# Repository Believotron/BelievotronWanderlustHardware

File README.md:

# Believotron Wanderlust Hardware
The source and output files for the Believotron Wanderlust synthesizer controller.

For more information:
http://believotron.com
http://community.believotron.community

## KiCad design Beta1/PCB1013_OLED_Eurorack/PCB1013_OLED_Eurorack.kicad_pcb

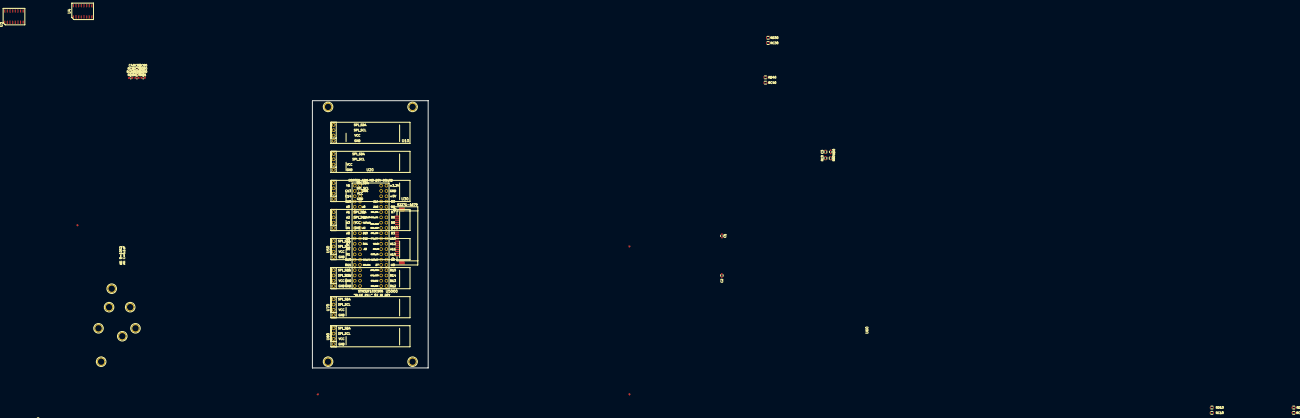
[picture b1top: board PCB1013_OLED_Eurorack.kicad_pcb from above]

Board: 2 copper layers, 55.6 x 128.5 mm, 38 parts (0 on the bottom side), 25 nets, no tracks yet.

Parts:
C1, C2, C3: 0.1u; C_0603
C4: 0.1u; C_0603_1608Metric
J2: FPC_20POS; FFC_1MM_20POS_MOLEX_52271-2079
RC0, RC10, RC20, RC30, RC40: 10K; R_0603
RC1, RC50, RC60, RC70, RC80: 10K; R_0603_1608Metric
RD0, RD10, RD20, RD30, RD40: 10K; R_0603
RD1, RD50, RD60, RD70, RD80: 10K; R_0603_1608Metric
RR0: 10K; R_0603
RR1: 10K; R_0603_1608Metric
U3, U4: I2C_1x4MUX_TCA9546A; SOIC-16_1.27x5.4
U10, U20, U30, U40, U50, U60, U70, U80: OLED_128x32_I2C; OLED_128x32
U5000: STM32F103C8T6_BLUE_PILL; BLUEPILL_CORTEXM3_STM32F103C8T6_THIN

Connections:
+3V3: C1.1, C2.1, C3.1, C4.1, J2.19, J2.20, RC0.1, RC1.1, RC10.1, RC20.1, RC30.1, RC40.1, RC50.1, RC60.1, RC70.1, RC80.1, RD0.1, RD1.1, RD10.1, RD20.1, RD30.1, RD40.1, RD50.1, RD60.1, RD70.1, RD80.1, RR0.1, RR1.1, U3.16, U4.16, U10.2, U20.2, U30.2, U40.2, U50.2, U60.2, U70.2, U80.2, U5000.3.3V
/!OLED_RESET: RR0.2, RR1.2, U3.3, U4.3, U5000.A7
/I2C_SCL0: RC10.2, U3.5, U10.3
/I2C_SCL1: RC20.2, U3.7, U20.3
/I2C_SCL2: RC30.2, U3.10, U30.3
/I2C_SCL3: RC40.2, U3.12, U40.3
/I2C_SCL4: RC50.2, U4.5, U50.3
/I2C_SCL5: RC60.2, U4.7, U60.3
/I2C_SCL6: RC70.2, U4.10, U70.3
/I2C_SCL7: RC80.2, U4.12, U80.3
/I2C_SCL_EXT: RC0.2, RC1.2, U3.14, U4.14, U5000.B10
/I2C_SDA0: RD10.2, U3.4, U10.4
/I2C_SDA1: RD20.2, U3.6, U20.4
/I2C_SDA2: RD30.2, U3.9, U30.4
/I2C_SDA3: RD40.2, U3.11, U40.4
/I2C_SDA4: RD50.2, U4.4, U50.4
/I2C_SDA5: RD60.2, U4.6, U60.4
/I2C_SDA6: RD70.2, U4.9, U70.4
/I2C_SDA7: RD80.2, U4.11, U80.4
/I2C_SDA_AXO: J2.4, U5000.B7
/I2C_SDA_EXT: RD0.2, RD1.2, U3.15, U4.15, U5000.B11
/RESET_AXO: J2.17, U5000.R
/RX_AXO: J2.8, U5000.A9
/TX_AXO: J2.9, U5000.A10
GND: C1.2, C2.2, C3.2, C4.2, J2.1, J2.2, U3.1, U3.2, U3.8, U3.13, U4.2, U4.8, U4.13, U10.1, U20.1, U30.1, U40.1, U50.1, U60.1, U70.1, U80.1, U5000.GND

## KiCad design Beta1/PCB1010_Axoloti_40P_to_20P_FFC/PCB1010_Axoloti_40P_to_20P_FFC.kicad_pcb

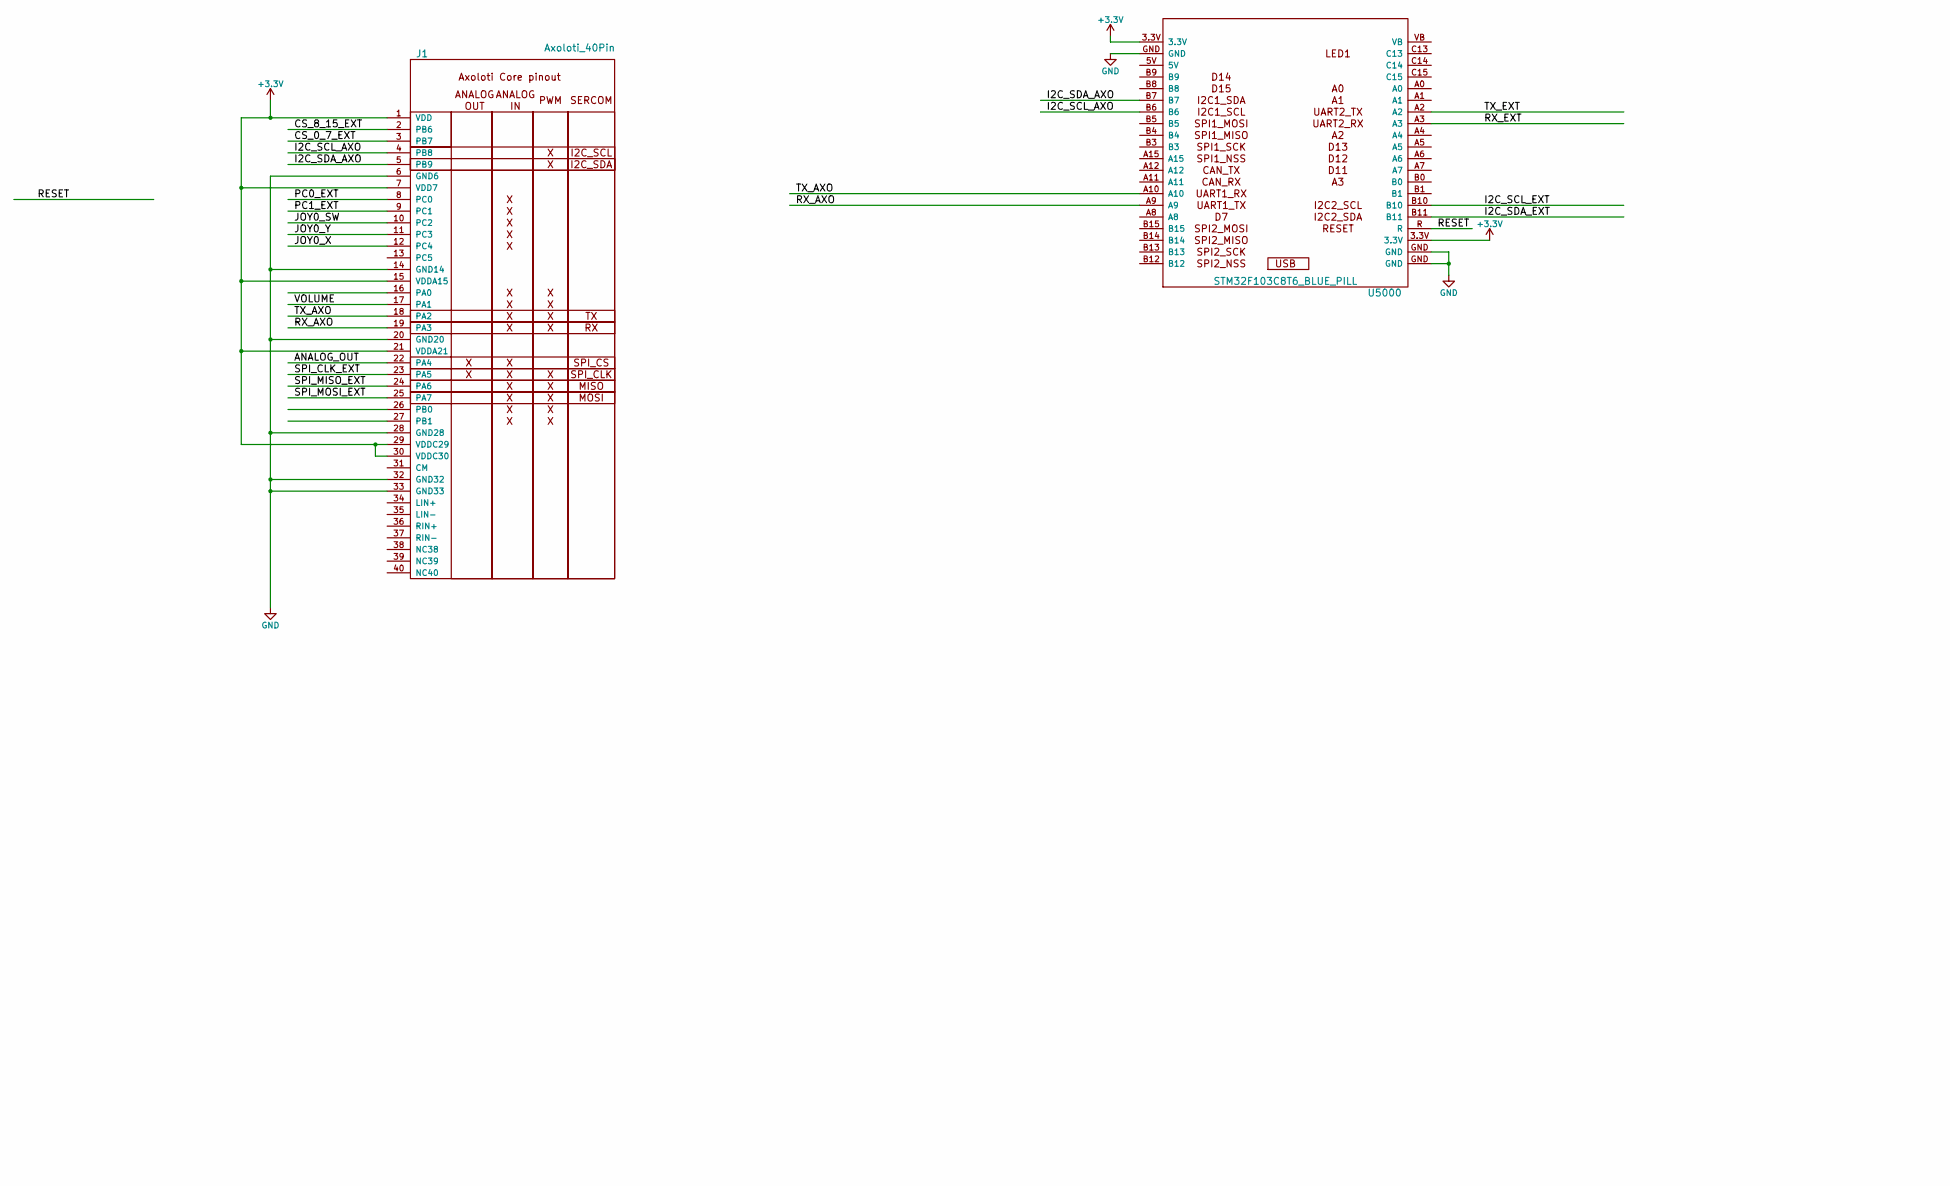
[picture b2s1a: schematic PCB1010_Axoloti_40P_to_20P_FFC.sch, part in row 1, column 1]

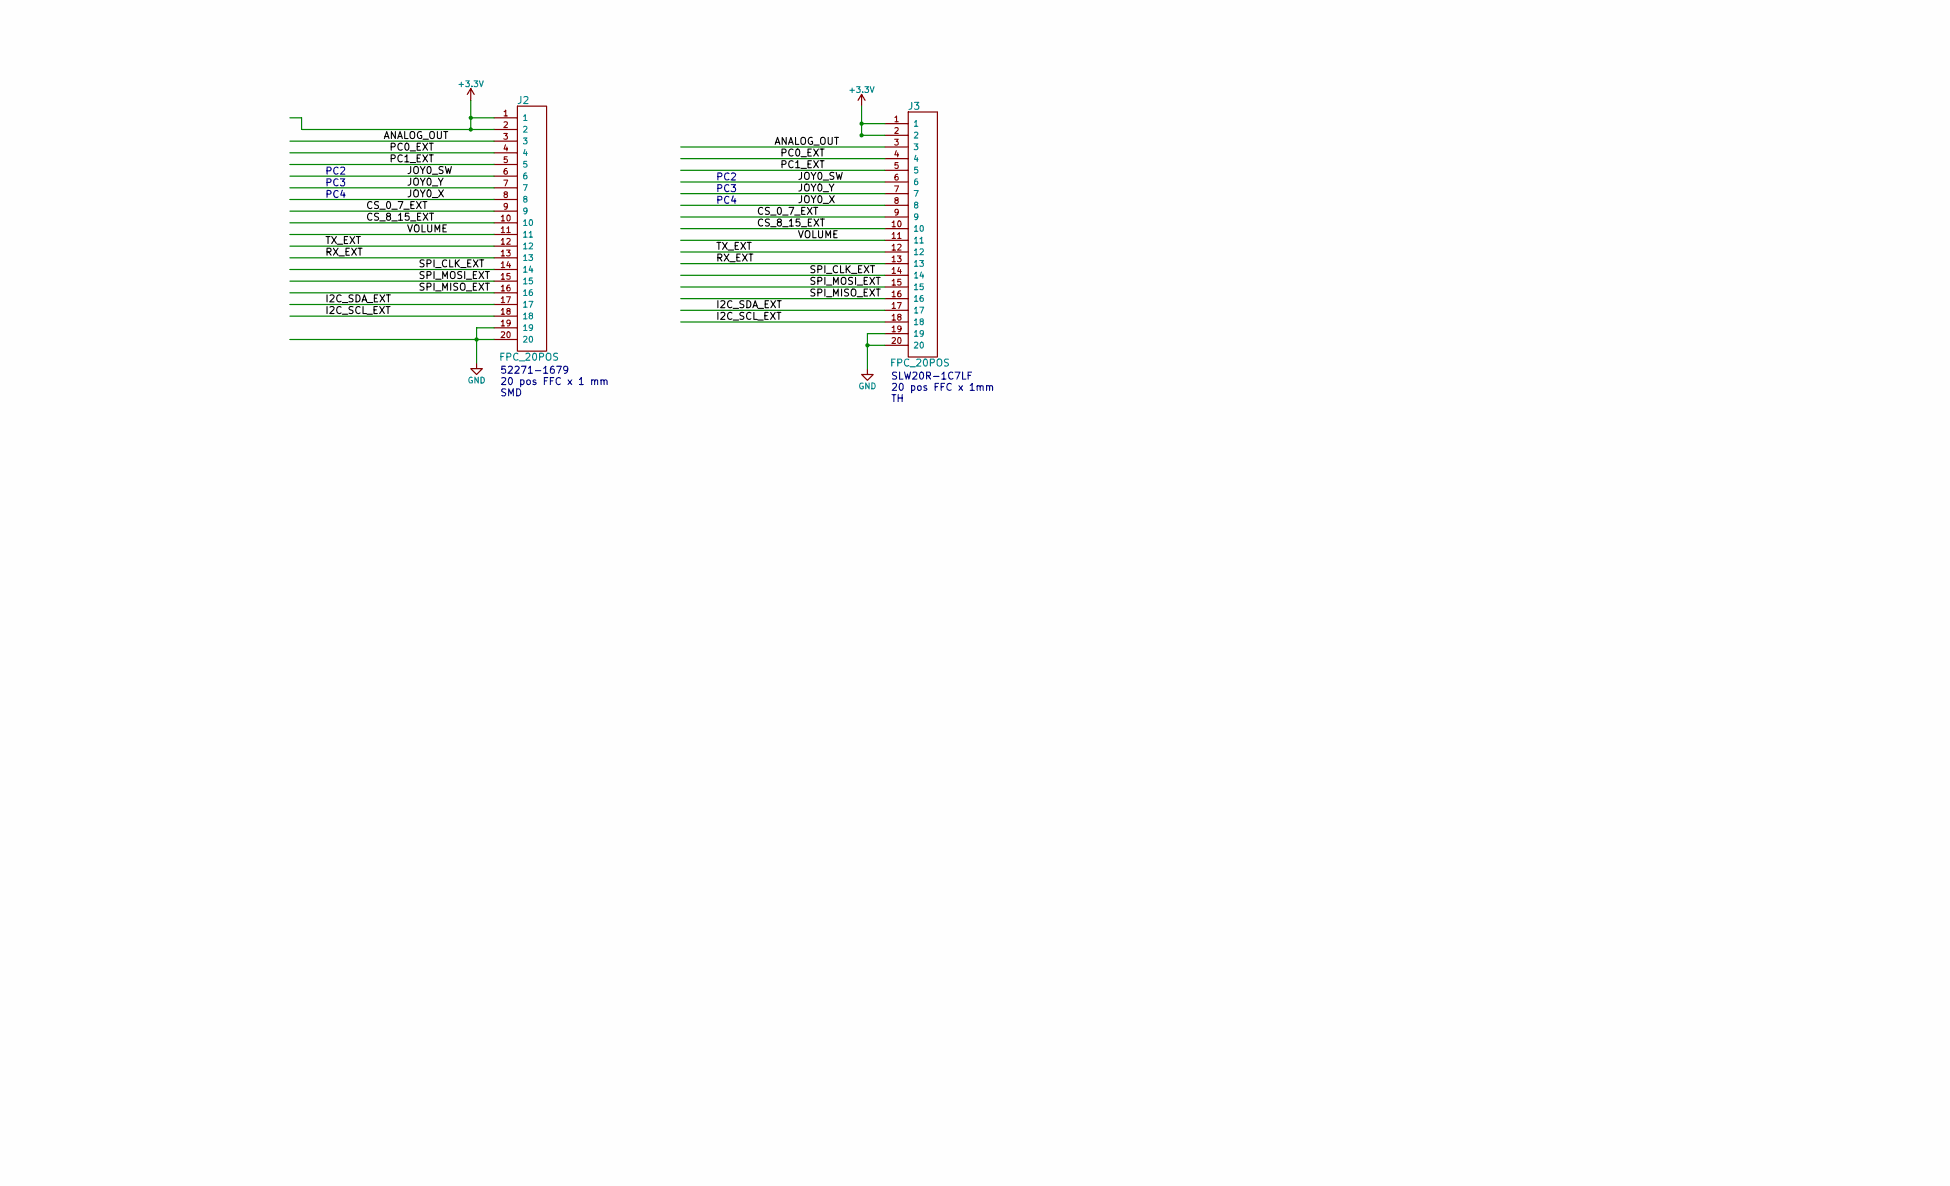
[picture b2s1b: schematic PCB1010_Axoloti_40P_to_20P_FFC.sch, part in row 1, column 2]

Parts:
J1: Axoloti_40Pin; Axoloti-40x2_slim
J2: FPC_20POS; FFC_1MM_20POS_MOLEX_52271-2079
J3: FPC_20POS; FFC_20x1mm_SLW20R-1C7LF
U5000: STM32F103C8T6_BLUE_PILL; BLUEPILL_CORTEXM3_STM32F103C8T6_THIN

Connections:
+3V3: J1.1 (VDD), J1.7 (VDD7), J1.15 (VDDA15), J1.21 (VDDA21), J1.29 (VDDC29), J1.30 (VDDC30), J2.1, J2.2, J3.1, J3.2, U5000.3.3V
/ANALOG_OUT: J1.22 (PA4), J2.3, J3.3
/CS_0_7_EXT: J1.3 (PB7), J2.9, J3.9
/CS_8_15_EXT: J1.2 (PB6), J2.10, J3.10
/I2C_SCL_AXO: J1.4 (PB8), U5000.B6
/I2C_SCL_EXT: J2.18, J3.18, U5000.B10
/I2C_SDA_AXO: J1.5 (PB9), U5000.B7
/I2C_SDA_EXT: J2.17, J3.17, U5000.B11
/JOY0_SW: J1.10 (PC2), J2.6, J3.6
/JOY0_X: J1.12 (PC4), J2.8, J3.8
/JOY0_Y: J1.11 (PC3), J2.7, J3.7
/PC0_EXT: J1.8 (PC0), J2.4, J3.4
/PC1_EXT: J1.9 (PC1), J2.5, J3.5
/RESET: U5000.R
/RX_AXO: J1.19 (PA3), U5000.A9
/RX_EXT: J2.13, J3.13, U5000.A3
/SPI_CLK_EXT: J1.23 (PA5), J2.14, J3.14
/SPI_MISO_EXT: J1.24 (PA6), J2.16, J3.16
/SPI_MOSI_EXT: J1.25 (PA7), J2.15, J3.15
/TX_AXO: J1.18 (PA2), U5000.A10
/TX_EXT: J2.12, J3.12, U5000.A2
/VOLUME: J1.17 (PA1), J2.11, J3.11
GND: J1.6 (GND6), J1.14 (GND14), J1.20 (GND20), J1.28 (GND28), J1.32 (GND32), J1.33 (GND33), J2.19, J2.20, J3.19, J3.20, U5000.GND

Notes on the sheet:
2017-06-07
Believotron KnobCore 8CH Knob + Vol + 4CH Joy + 3CH OLED
Open source via MIT License github.com/Believotron/BelievotronWanderlustHardware
Date
PC2
PC3
PC4
SLW20R-1C7LF 20 pos FFC x 1mm TH
52271-1679 20 pos FFC x 1 mm SMD

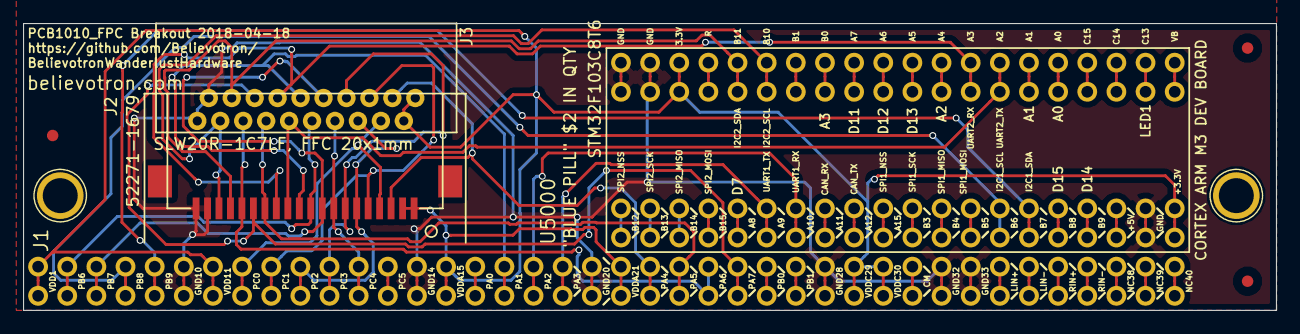
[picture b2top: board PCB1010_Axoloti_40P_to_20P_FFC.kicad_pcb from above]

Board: 2 copper layers, 109.2 x 25.0 mm, 4 parts (0 on the bottom side), 22 nets.

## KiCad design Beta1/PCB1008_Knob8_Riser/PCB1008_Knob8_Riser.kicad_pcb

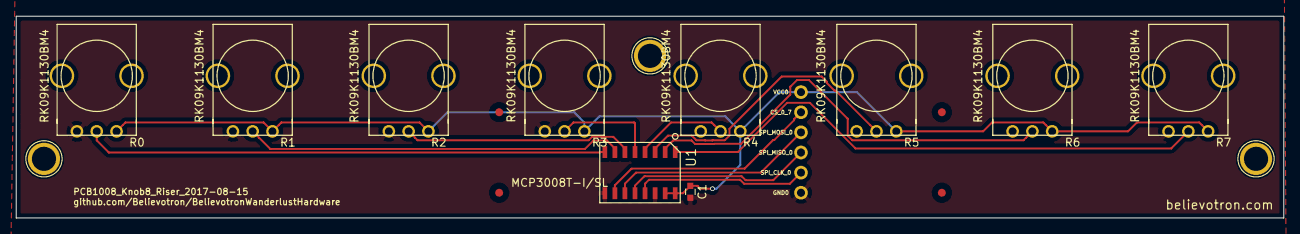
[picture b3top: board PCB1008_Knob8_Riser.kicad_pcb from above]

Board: 2 copper layers, 160.0 x 25.5 mm, 16 parts (0 on the bottom side), 14 nets.

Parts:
C1: 0.1u; C_0603
CS_0_7: CONN_01X01; single_0.1
GND0: CONN_01X01; single_0.1
R0, R1, R2, R3, R4, R5, R6, R7: POT; POT_ALPS_RK09K1130BM4
SPI_CLK_0: CONN_01X01; single_0.1
SPI_MISO_0: CONN_01X01; single_0.1
SPI_MOSI_0: CONN_01X01; single_0.1
U1: MCP3008T-I/SL; SOIC-16
VCC0: CONN_01X01; single_0.1

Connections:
+3V3: C1.1, R0.1, R1.1, R2.1, R3.1, R4.1, R5.1, R6.1, R7.1, U1.15, U1.16, VCC0.1
/CS_0_7: CS_0_7.1, U1.10
/P0: R0.2, U1.8
/P1: R1.2, U1.7
/P2: R2.2, U1.6
/P3: R3.2, U1.5
/P4: R4.2, U1.4
/P5: R5.2, U1.3
/P6: R6.2, U1.2
/P7: R7.2, U1.1
/SPI_CLK: SPI_CLK_0.1, U1.13
/SPI_MISO: SPI_MISO_0.1, U1.12
/SPI_MOSI: SPI_MOSI_0.1, U1.11
GND: C1.2, GND0.1, R0.3, R1.3, R2.3, R3.3, R4.3, R5.3, R6.3, R7.3, U1.9, U1.14

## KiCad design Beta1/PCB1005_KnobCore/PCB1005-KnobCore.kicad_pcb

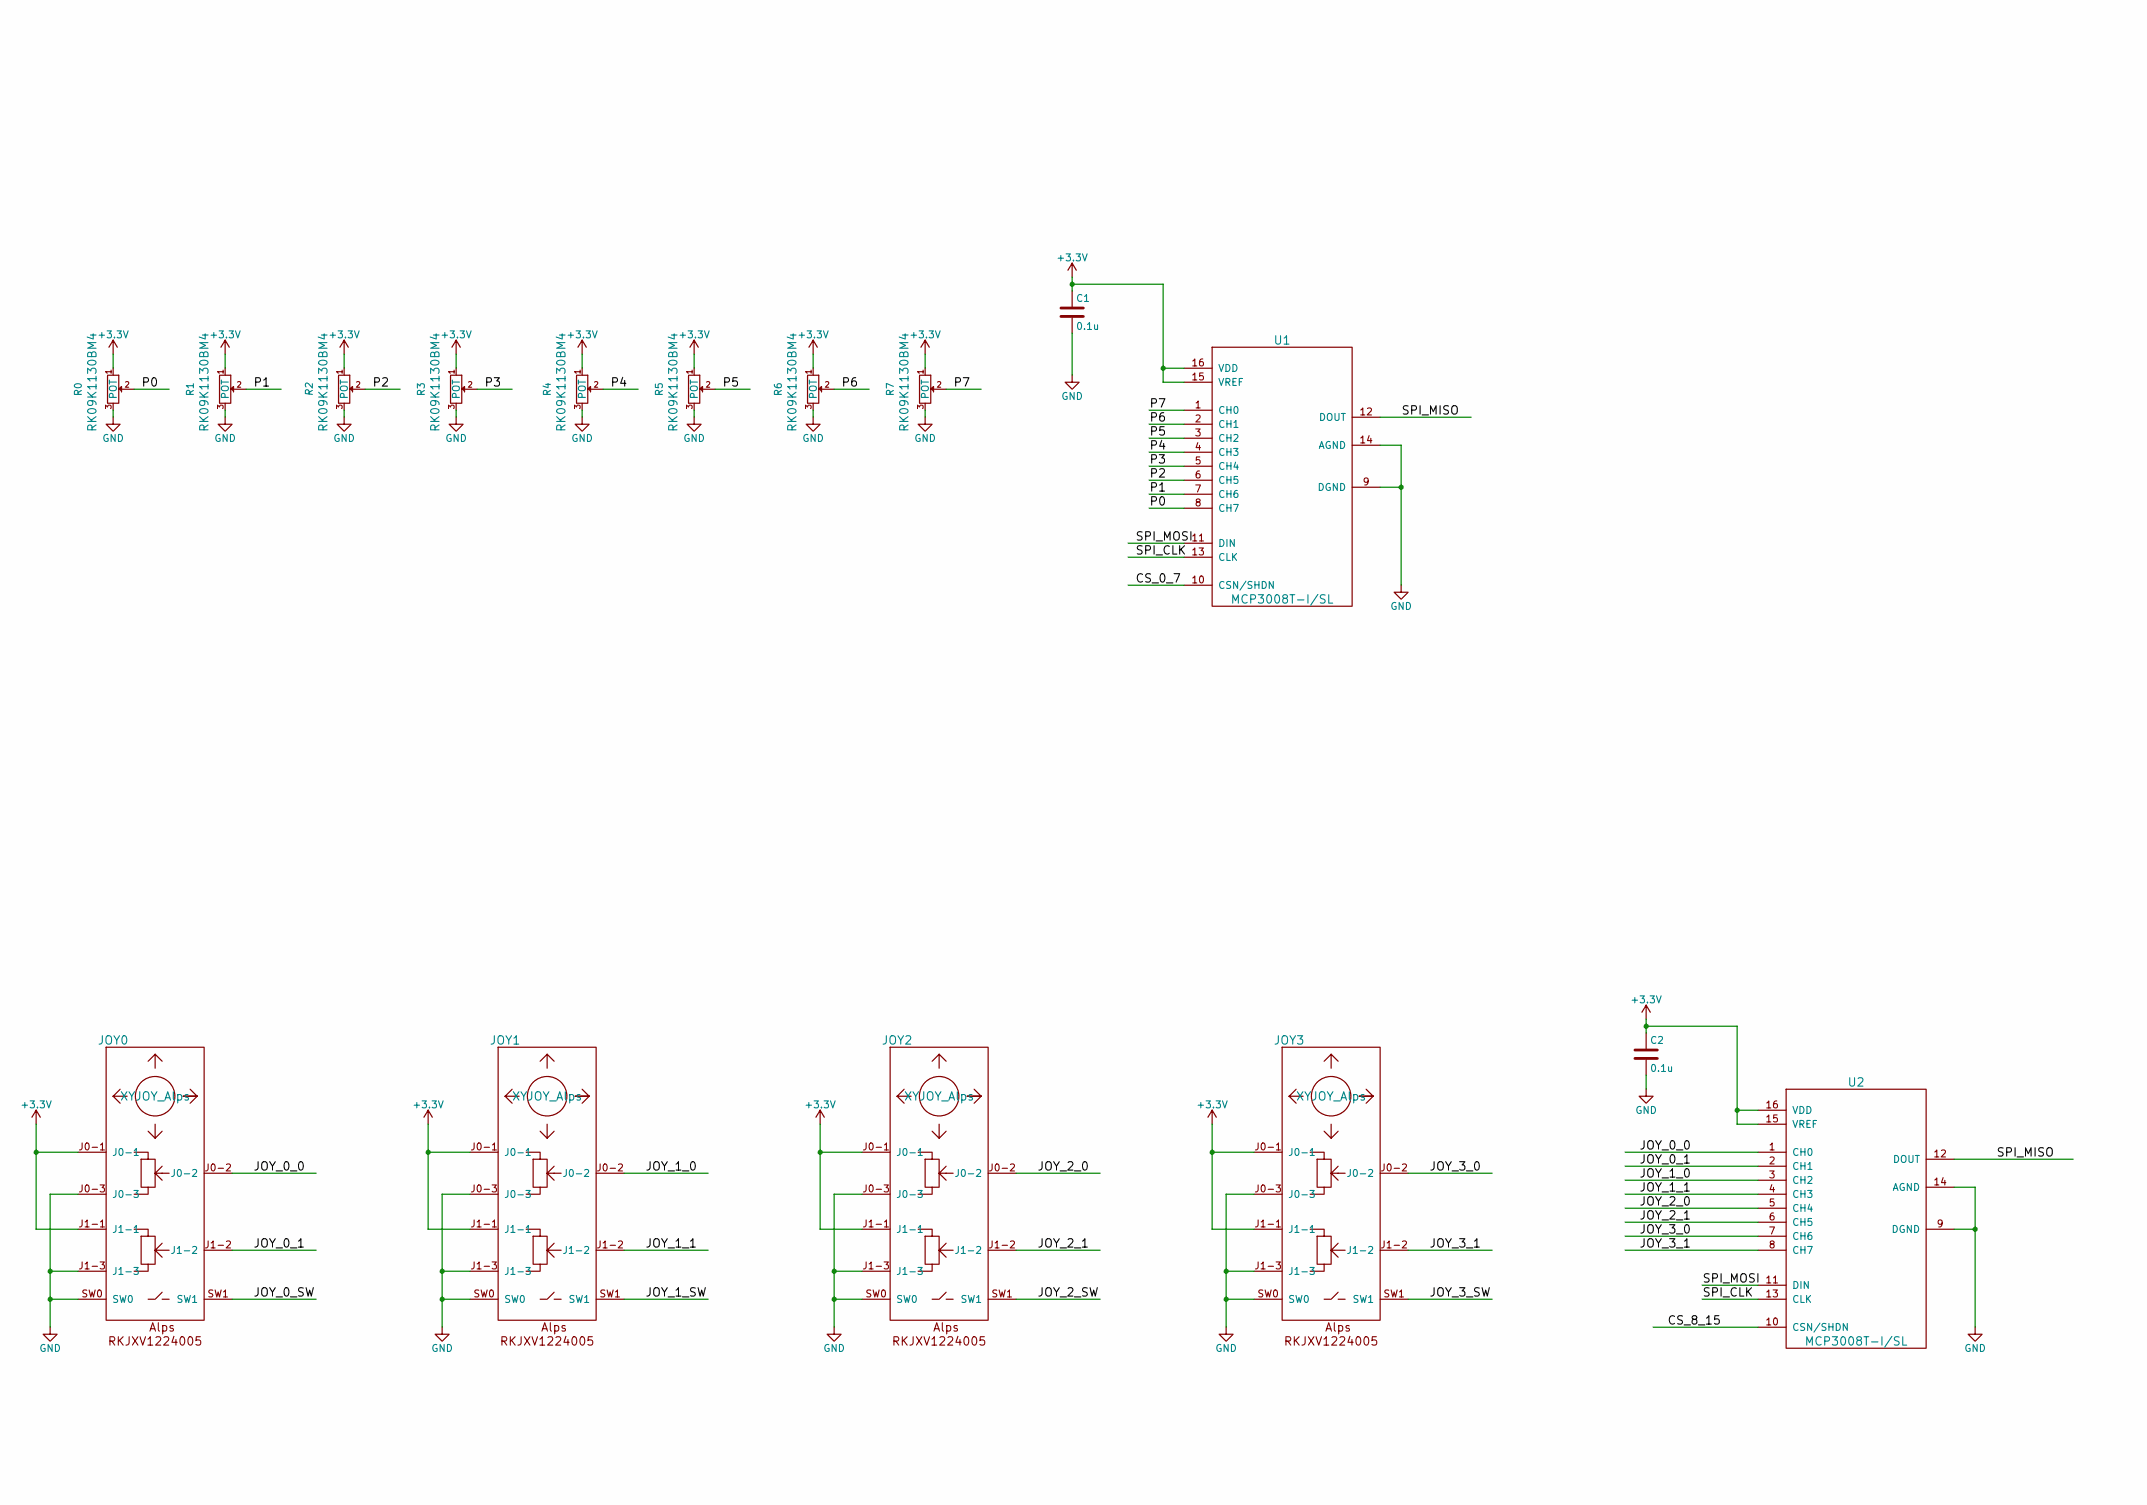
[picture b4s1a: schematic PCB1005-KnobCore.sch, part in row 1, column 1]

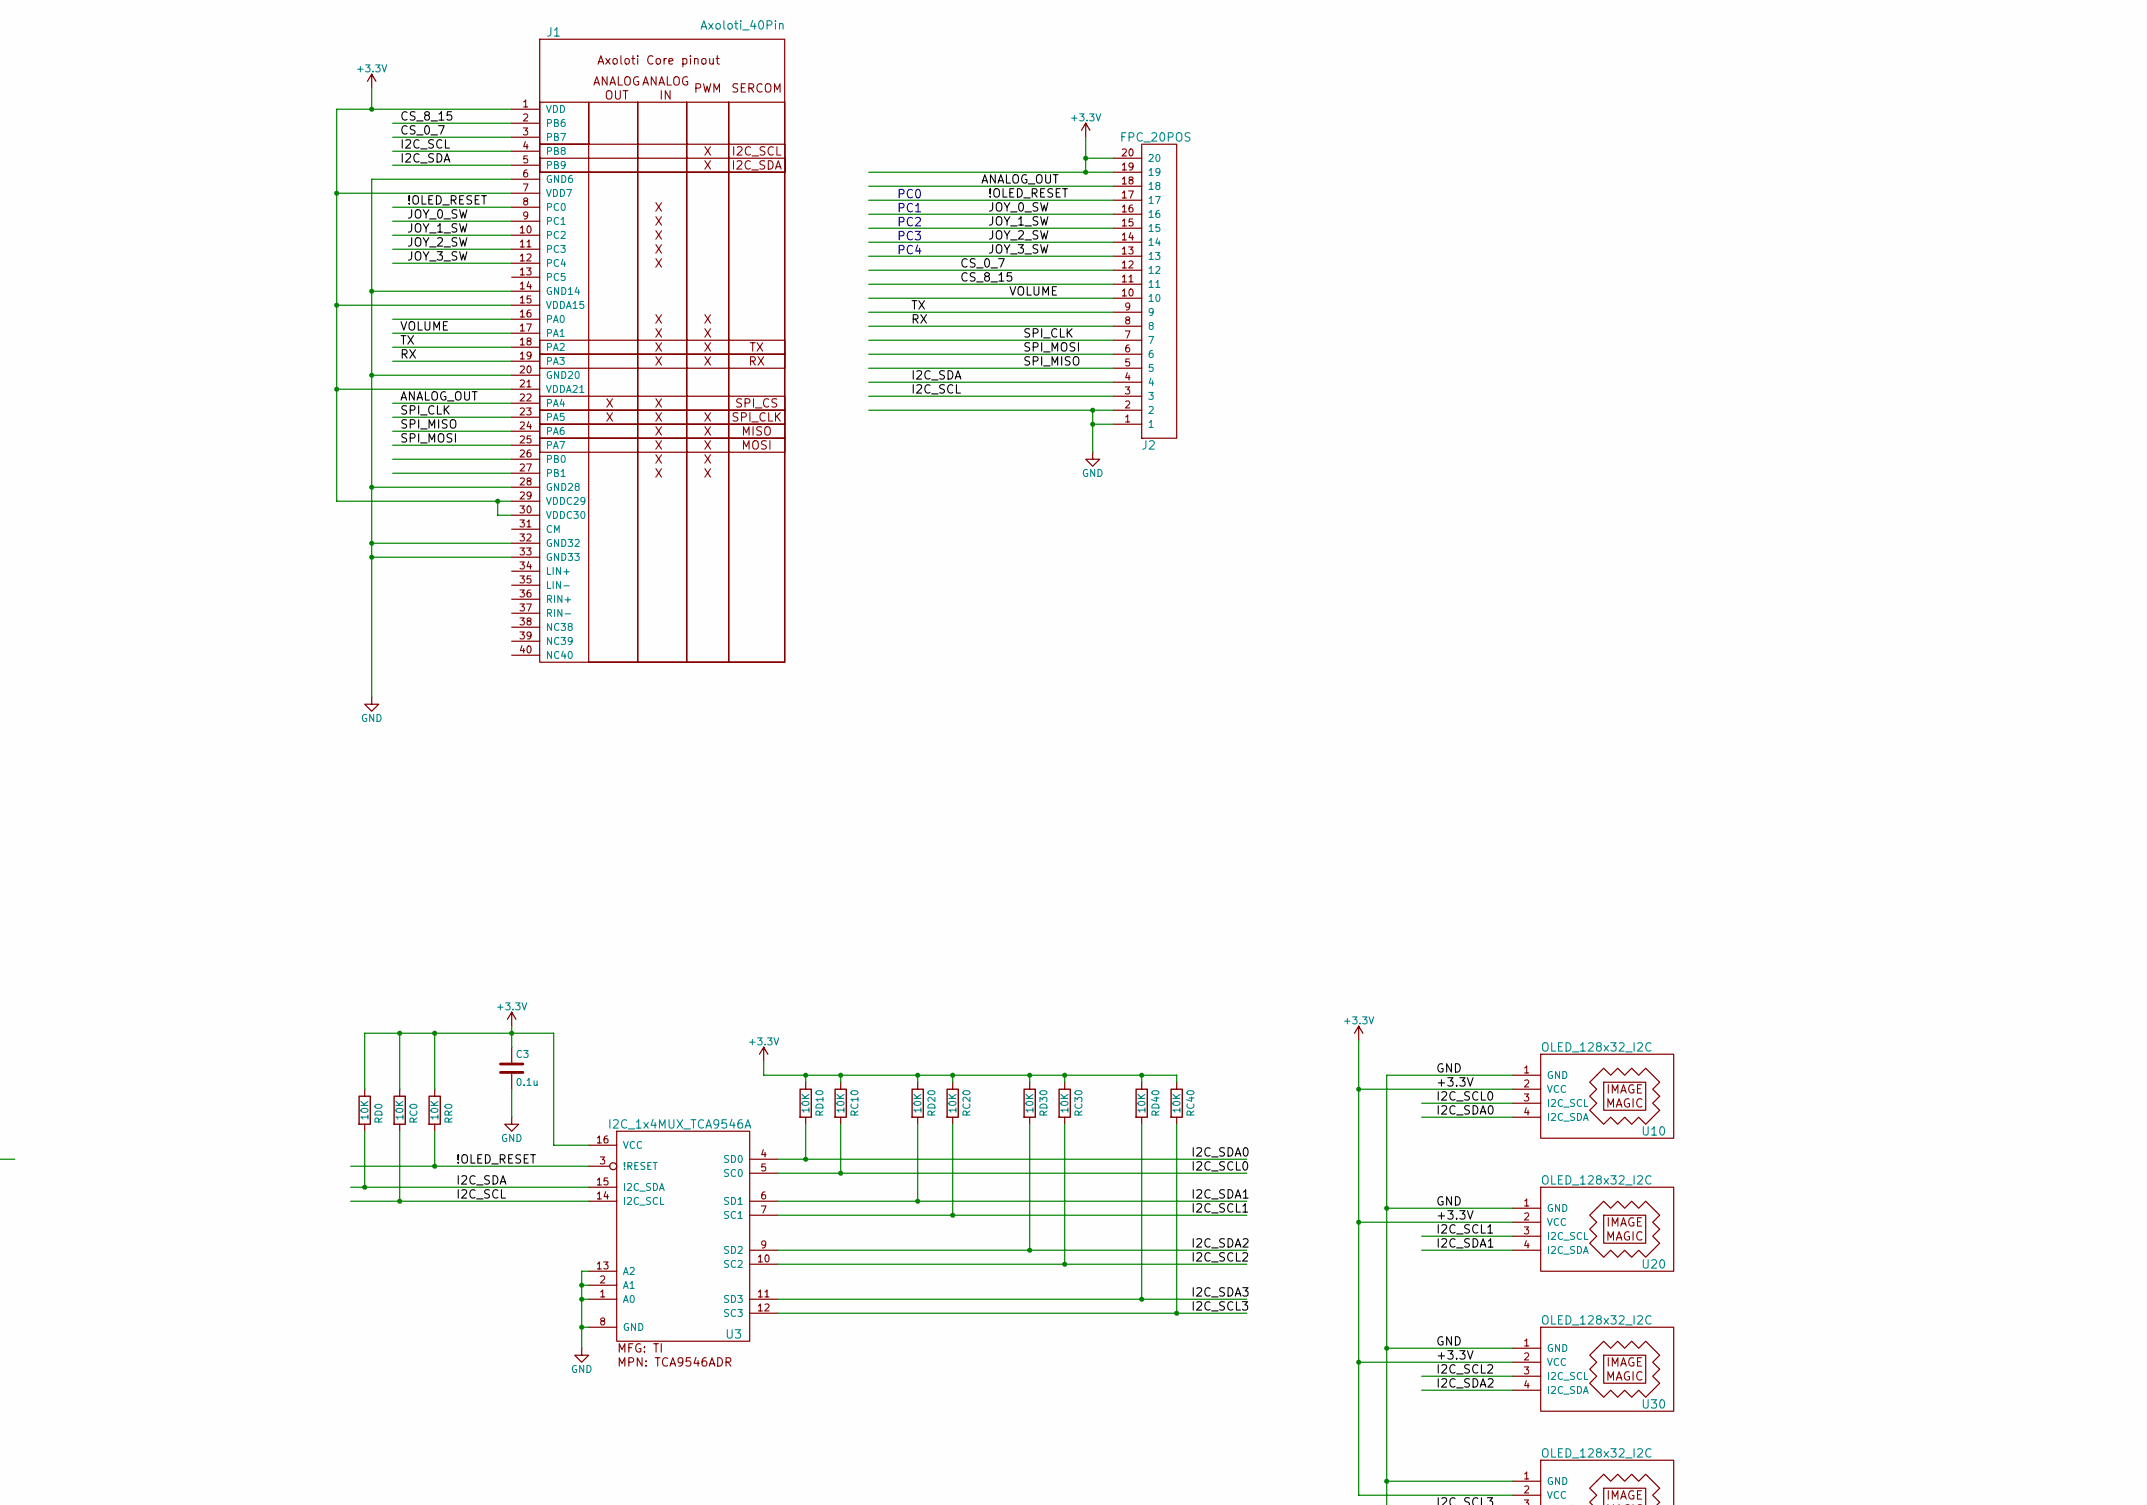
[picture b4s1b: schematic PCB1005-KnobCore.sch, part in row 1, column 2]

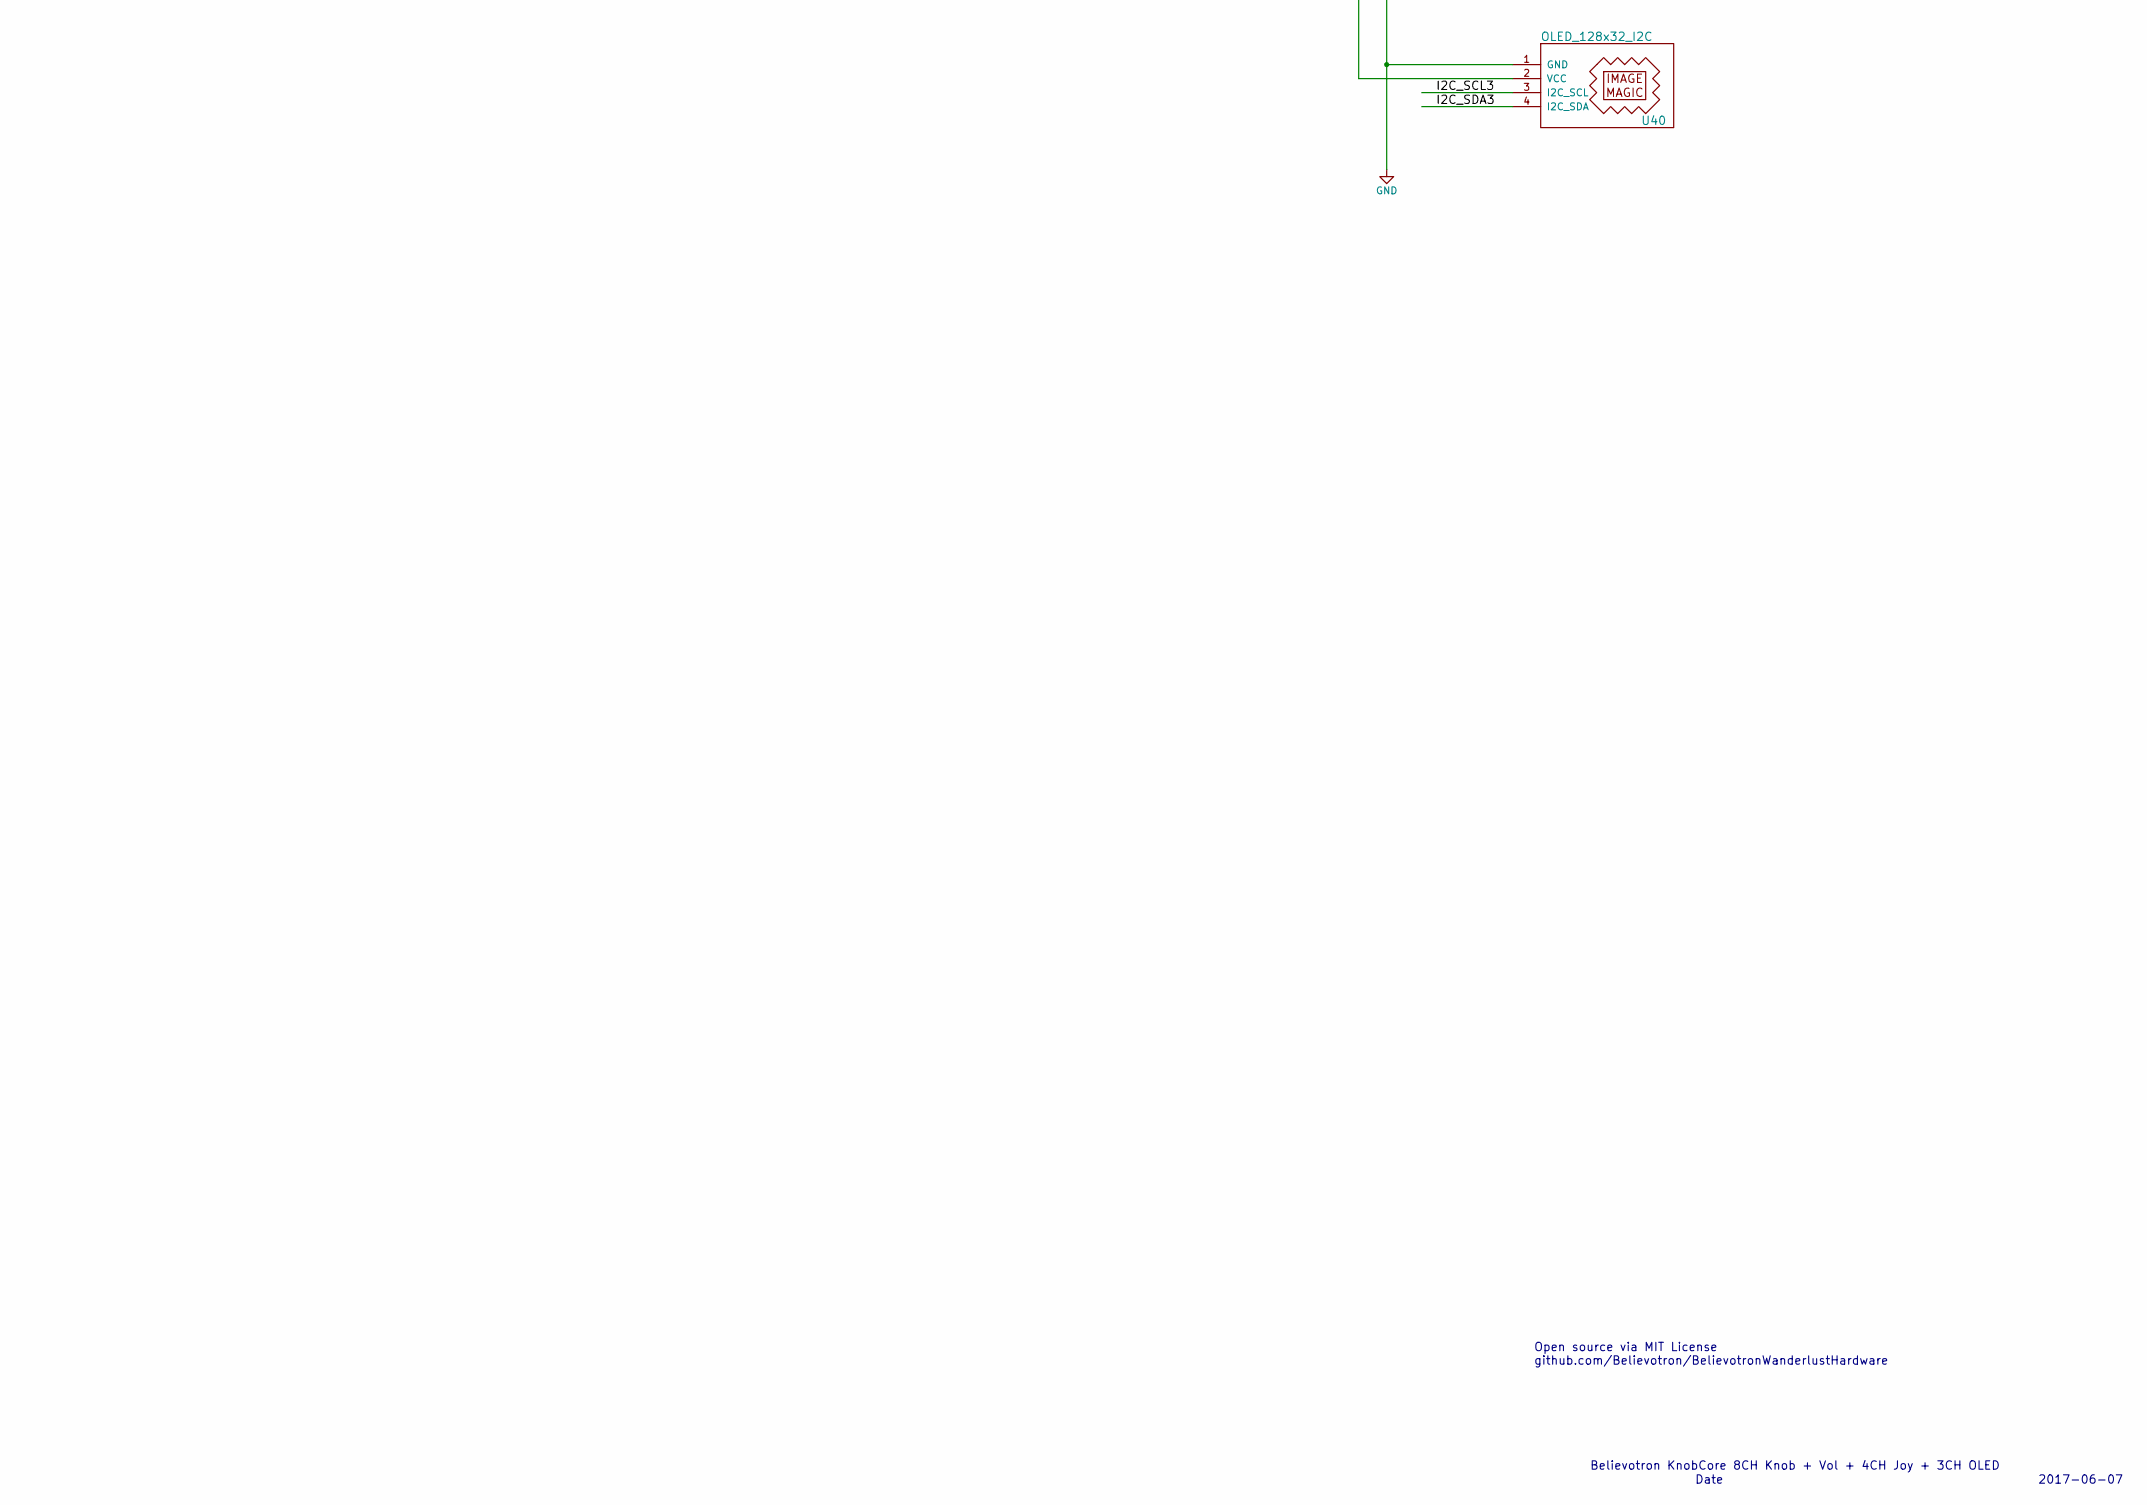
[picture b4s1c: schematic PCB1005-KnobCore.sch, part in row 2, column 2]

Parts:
C1, C2, C3: 0.1u; C_0603; MPN CC0603KRX7R9BB104
J1: Axoloti_40Pin; Axoloti-40x1_slim
J2: FPC_20POS; FFC_1MM_20POS_MOLEX_52271-2079
JOY0, JOY1, JOY2, JOY3: XYJOY_Alps; JOY_ALPS_RKJXV1224005
R0, R1, R2, R3, R4, R5, R6, R7: POT; POT_ALPS_RK09K1130BM4; MPN RK09K1130BM4
RC0, RC10, RC20, RC30, RC40: 10K; R_0603; MPN CRCW060310K0JNEA
RD0, RD10, RD20, RD30, RD40: 10K; R_0603; MPN CRCW060310K0JNEA
RR0: 10K; R_0603; MPN CRCW060310K0JNEA
U1, U2: MCP3008T-I/SL; SOIC-16; MPN MCP3008T-I/SL
U3: I2C_1x4MUX_TCA9546A; SOIC-16_1.27x5.4
U10, U20, U30, U40: OLED_128x32_I2C; OLED_128x32

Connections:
+3V3: C1.1, C2.1, C3.1, J1.1 (VDD), J1.7 (VDD7), J1.15 (VDDA15), J1.21 (VDDA21), J1.29 (VDDC29), J1.30 (VDDC30), J2.19, J2.20, JOY0.J0-1, JOY0.J1-1, JOY1.J0-1, JOY1.J1-1, JOY2.J0-1, JOY2.J1-1, JOY3.J0-1, JOY3.J1-1, R0.1, R1.1, R2.1, R3.1, R4.1, R5.1, R6.1, R7.1, RC0.1, RC10.1, RC20.1, RC30.1, RC40.1, RD0.1, RD10.1, RD20.1, RD30.1, RD40.1, RR0.1, U1.15 (VREF), U1.16 (VDD), U2.15 (VREF), U2.16 (VDD), U3.16 (VCC), U10.2 (VCC), U20.2 (VCC), U30.2 (VCC), U40.2 (VCC)
/!OLED_RESET: J1.8 (PC0), J2.17, RR0.2, U3.3 (!RESET)
/ANALOG_OUT: J1.22 (PA4), J2.18
/CS_0_7: J1.3 (PB7), J2.12, U1.10 (CSN/SHDN)
/CS_8_15: J1.2 (PB6), J2.11, U2.10 (CSN/SHDN)
/I2C_SCL: J1.4 (PB8), J2.3, RC0.2, U3.14 (I2C_SCL)
/I2C_SCL0: RC10.2, U3.5 (SC0), U10.3 (I2C_SCL)
/I2C_SCL1: RC20.2, U3.7 (SC1), U20.3 (I2C_SCL)
/I2C_SCL2: RC30.2, U3.10 (SC2), U30.3 (I2C_SCL)
/I2C_SCL3: RC40.2, U3.12 (SC3), U40.3 (I2C_SCL)
/I2C_SDA: J1.5 (PB9), J2.4, RD0.2, U3.15 (I2C_SDA)
/I2C_SDA0: RD10.2, U3.4 (SD0), U10.4 (I2C_SDA)
/I2C_SDA1: RD20.2, U3.6 (SD1), U20.4 (I2C_SDA)
/I2C_SDA2: RD30.2, U3.9 (SD2), U30.4 (I2C_SDA)
/I2C_SDA3: RD40.2, U3.11 (SD3), U40.4 (I2C_SDA)
/JOY_0_0: JOY0.J0-2, U2.1 (CH0)
/JOY_0_1: JOY0.J1-2, U2.2 (CH1)
/JOY_0_SW: J1.9 (PC1), J2.16, JOY0.SW1
/JOY_1_0: JOY1.J0-2, U2.3 (CH2)
/JOY_1_1: JOY1.J1-2, U2.4 (CH3)
/JOY_1_SW: J1.10 (PC2), J2.15, JOY1.SW1
/JOY_2_0: JOY2.J0-2, U2.5 (CH4)
/JOY_2_1: JOY2.J1-2, U2.6 (CH5)
/JOY_2_SW: J1.11 (PC3), J2.14, JOY2.SW1
/JOY_3_0: JOY3.J0-2, U2.7 (CH6)
/JOY_3_1: JOY3.J1-2, U2.8 (CH7)
/JOY_3_SW: J1.12 (PC4), J2.13, JOY3.SW1
/P0: R0.2, U1.8 (CH7)
/P1: R1.2, U1.7 (CH6)
/P2: R2.2, U1.6 (CH5)
/P3: R3.2, U1.5 (CH4)
/P4: R4.2, U1.4 (CH3)
/P5: R5.2, U1.3 (CH2)
/P6: R6.2, U1.2 (CH1)
/P7: R7.2, U1.1 (CH0)
/RX: J1.19 (PA3), J2.8
/SPI_CLK: J1.23 (PA5), J2.7, U1.13 (CLK), U2.13 (CLK)
/SPI_MISO: J1.24 (PA6), J2.5, U1.12 (DOUT), U2.12 (DOUT)
/SPI_MOSI: J1.25 (PA7), J2.6, U1.11 (DIN), U2.11 (DIN)
/TX: J1.18 (PA2), J2.9
/VOLUME: J1.17 (PA1), J2.10
GND: C1.2, C2.2, C3.2, J1.6 (GND6), J1.14 (GND14), J1.20 (GND20), J1.28 (GND28), J1.32 (GND32), J1.33 (GND33), J2.1, J2.2, JOY0.J0-3, JOY0.J1-3, JOY0.SW0, JOY1.J0-3, JOY1.J1-3, JOY1.SW0, JOY2.J0-3, JOY2.J1-3, JOY2.SW0, JOY3.J0-3, JOY3.J1-3, JOY3.SW0, R0.3, R1.3, R2.3, R3.3, R4.3, R5.3, R6.3, R7.3, U1.9 (DGND), U1.14 (AGND), U2.9 (DGND), U2.14 (AGND), U3.1 (A0), U3.2 (A1), U3.8 (GND), U3.13 (A2), U10.1 (GND), U20.1 (GND), U30.1 (GND), U40.1 (GND)

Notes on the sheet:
2017-06-07
Believotron KnobCore 8CH Knob + Vol + 4CH Joy + 3CH OLED
Open source via MIT License github.com/Believotron/BelievotronWanderlustHardware
Date
PC0
PC1
PC2
PC3
PC4

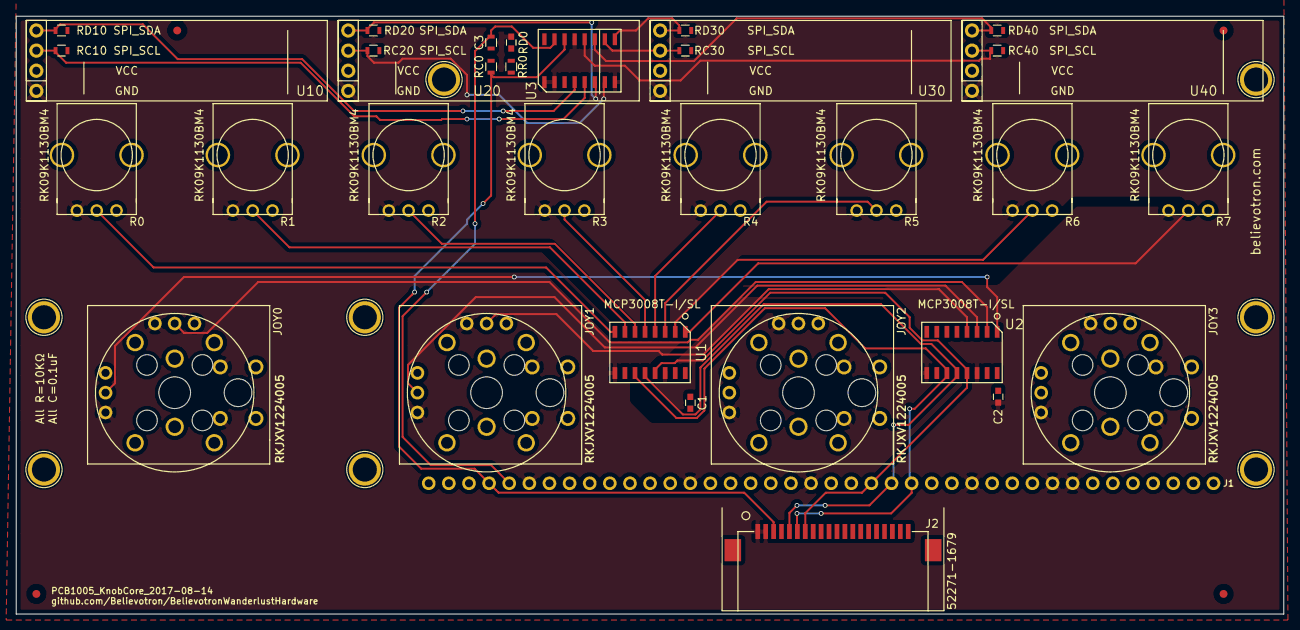
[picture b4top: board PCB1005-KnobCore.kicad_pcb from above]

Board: 2 copper layers, 160.0 x 75.5 mm, 35 parts (0 on the bottom side), 42 nets.

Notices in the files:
Beta1/PCB1005_KnobCore/PCB1005-KnobCore.kicad_pcb:
Open source MIT license files at: github.com/Believotron/BelievotronWanderlustHardware
